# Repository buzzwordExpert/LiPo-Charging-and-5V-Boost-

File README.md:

# Lithium Battery Charger and Boost Converter PCB

This PCB is designed to charge a 1S configuration LiPo Battery at 300mA and provide a stable 5V output.
Power Path Management is integrated using PMOS.
Only overcharge protection is supported.

# Features
- **CHarging IC**: TP4056 with 300mA of charge current.
- **Boost Converter**: MT3608 set to output 5V.
- **Power Path Mangement**: The PCB can simultaneouly charge the battery and provide output from input power provided. Integrated using a P Channel MOSFET.

# Images

**3D Renderings**
- Front View:

- Back View:

**PCB**

**2 Layer Board** - GND pour on both planes.

- Front Layer:

- Back Layer:

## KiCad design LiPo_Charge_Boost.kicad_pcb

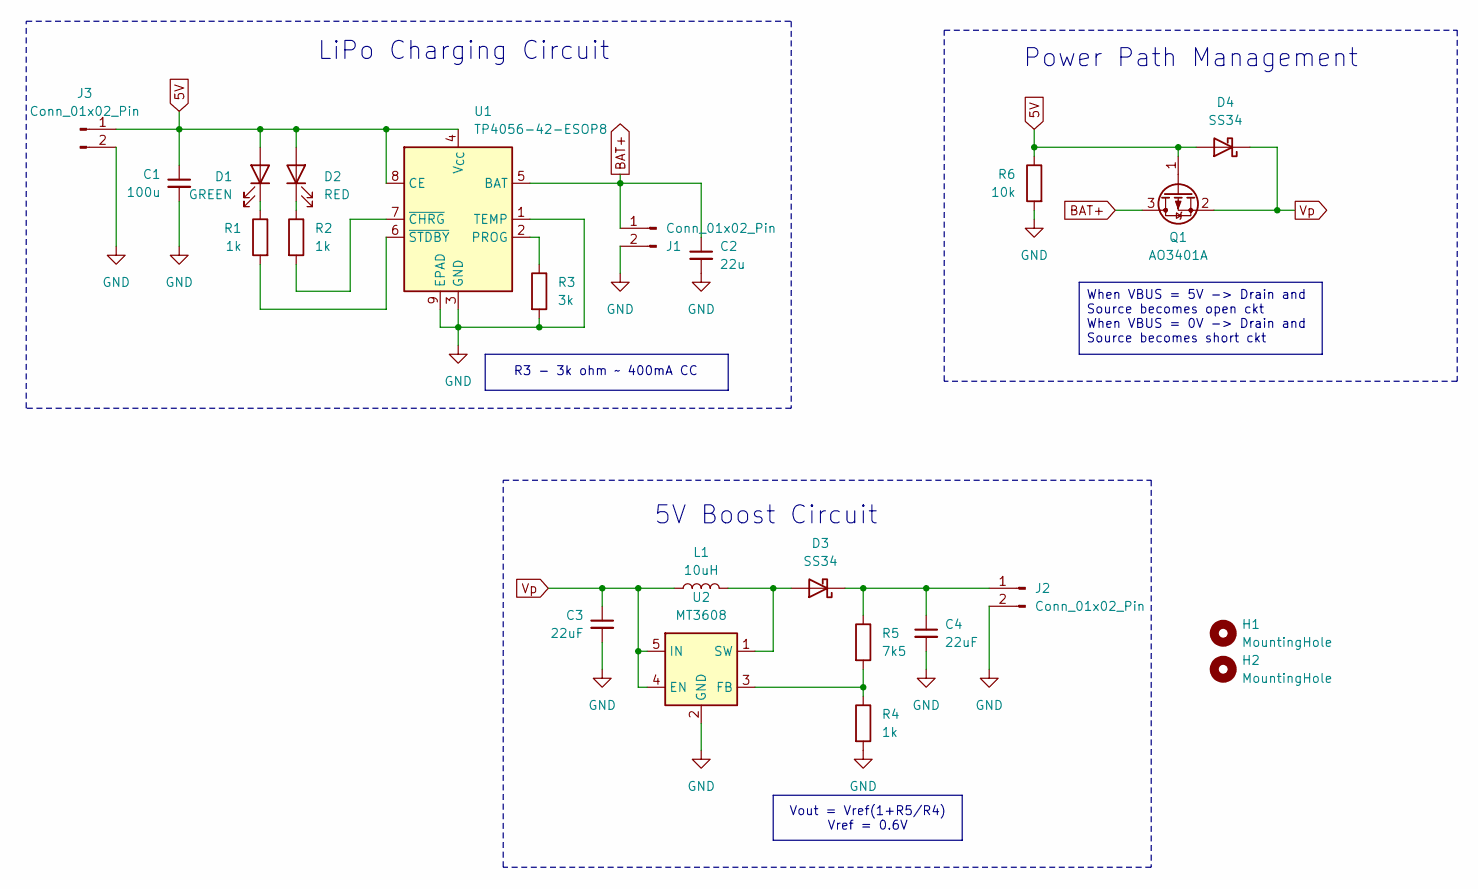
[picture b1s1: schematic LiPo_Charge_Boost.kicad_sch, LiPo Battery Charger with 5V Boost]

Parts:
C1: 100u; C_1206_3216Metric_Pad1.33x1.80mm_HandSolder
C2: 22u; C_1206_3216Metric_Pad1.33x1.80mm_HandSolder
C3, C4: 22uF; C_1206_3216Metric_Pad1.33x1.80mm_HandSolder
D1: GREEN; LED_1206_3216Metric_Pad1.42x1.75mm_HandSolder
D2: RED; LED_1206_3216Metric_Pad1.42x1.75mm_HandSolder
D3, D4: SS34; D_SMA
H1, H2: MountingHole; MountingHole_3.2mm_M3_DIN965_Pad_TopBottom
J1, J2, J3: Conn_01x02_Pin; JST_EH_B2B-EH-A_1x02_P2.50mm_Vertical
L1: 10uH; L_Abracon_ASPI-0630LR
Q1: AO3401A; SOT-23
R1, R2, R4: 1k; R_1206_3216Metric_Pad1.30x1.75mm_HandSolder
R3: 3k; R_1206_3216Metric_Pad1.30x1.75mm_HandSolder
R5: 7k5; R_1206_3216Metric_Pad1.30x1.75mm_HandSolder
R6: 10k; R_1206_3216Metric_Pad1.30x1.75mm_HandSolder
U1: TP4056-42-ESOP8; SOIC-8-1EP_3.9x4.9mm_P1.27mm_EP2.41x3.3mm_ThermalVias
U2: MT3608; SOT-23-6

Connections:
5V: C1.1, D1.2 (A), D2.2 (A), D4.2 (A), J3.1, Q1.1 (G), R6.1, U1.4 (V_{CC}), U1.8 (CE)
BAT+: C2.1, J1.1, Q1.3 (D), U1.5 (BAT)
GND: C1.2, C2.2, C3.2, C4.2, J1.2, J2.2, J3.2, R3.2, R4.2, R6.2, U1.1 (TEMP), U1.3 (GND), U1.9 (EPAD), U2.2 (GND)
unnamed: D1.1 (K), R1.1
unnamed: D2.1 (K), R2.1
unnamed: D3.2 (A), L1.2, U2.1 (SW)
unnamed: C4.1, D3.1 (K), J2.1, R5.1
unnamed: R3.1, U1.2 (PROG)
unnamed: R2.2, U1.7 (~CHRG)
unnamed: R1.2, U1.6 (~STDBY)
unnamed: R4.1, R5.2, U2.3 (FB)
Vp: C3.1, D4.1 (K), L1.1, Q1.2 (S), U2.4 (EN), U2.5 (IN)

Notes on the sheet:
Power Path Management
LiPo Charging Circuit
R3 - 3k ohm ~ 400mA CC
5V Boost Circuit
When VBUS = 5V -> Drain and Source becomes open ckt When VBUS = 0V -> Drain and Source becomes short ckt
Vout = Vref(1+R5/R4) Vref = 0.6V

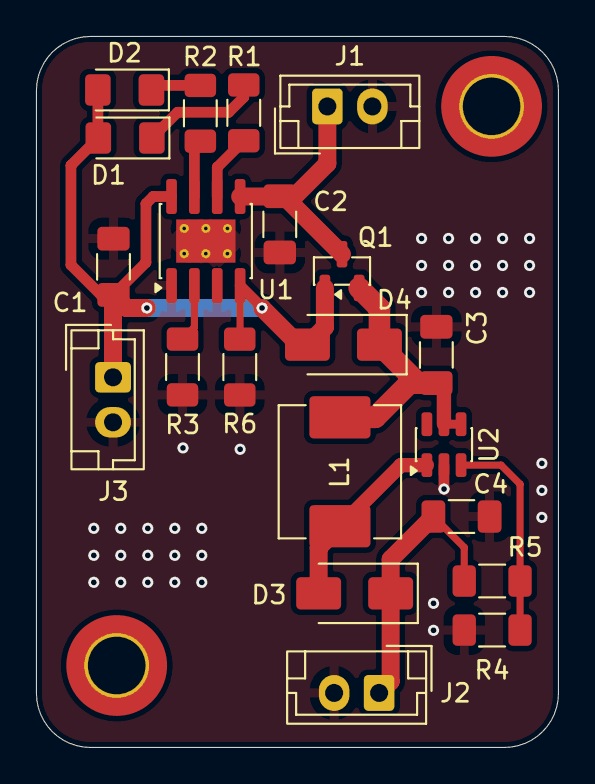
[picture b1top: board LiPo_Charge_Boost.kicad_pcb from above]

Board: 2 copper layers, 29.0 x 39.5 mm, 23 parts (0 on the bottom side), 12 nets.
